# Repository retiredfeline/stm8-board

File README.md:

# A quick and simple STM8 board with TCXO

A [quick and simple STM8 clock board with TCXO](https://hackaday.io/project/184120-quick-and-simple-stm8-board-with-tcxo) to be used in a larger project.

## Versioning

First release February 2022

## Authors

* **Ken Yap**

## License

See the [LICENSE](LICENSE.md) file for license rights and limitations (MIT).

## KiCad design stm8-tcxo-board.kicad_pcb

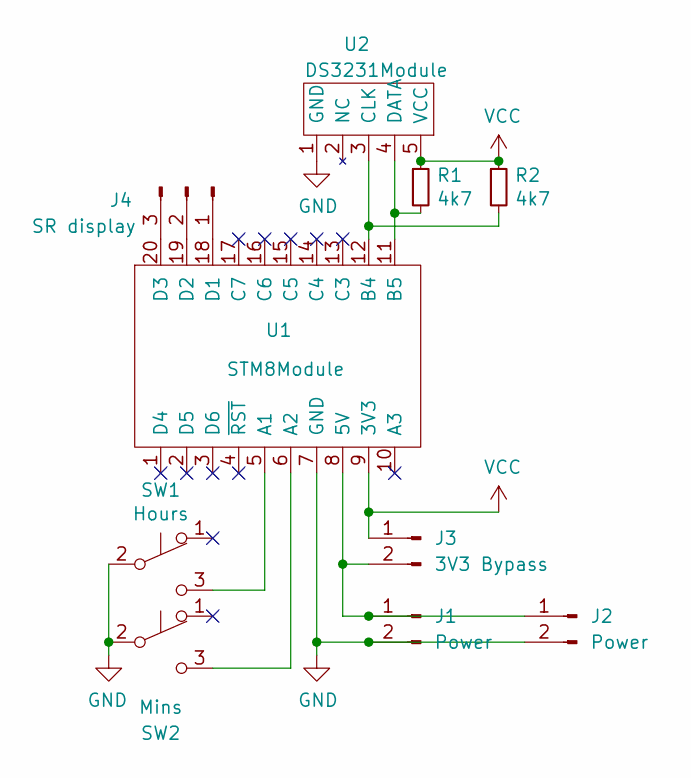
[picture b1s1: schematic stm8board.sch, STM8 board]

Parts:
J1, J2: Power; PinHeader_1x02_P2.54mm_Vertical
J3: 3V3 Bypass; PinHeader_1x02_P2.54mm_Vertical
J4: SR display; PinHeader_1x03_P2.54mm_Vertical
R1, R2: 4k7; R_Axial_DIN0207_L6.3mm_D2.5mm_P10.16mm_Horizontal
SW1: Hours; SWITCH_SPDT_PTH_11.6X4.0MM
SW2: Mins; SWITCH_SPDT_PTH_11.6X4.0MM
U1: STM8Module; DIP-20_600_ELL
U2: DS3231Module; DS3231_Module

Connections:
GND: J1.2, J2.2, SW1.2 (B), SW2.2 (B), U1.7 (GND), U2.1 (GND)
unnamed: J1.1, J2.1, J3.2, U1.8 (5V)
unnamed: J4.1, U1.18 (D1)
unnamed: J4.2, U1.19 (D2)
unnamed: J4.3, U1.20 (D3)
unnamed: R1.2, U1.11 (B5), U2.4 (DATA)
unnamed: R2.2, U1.12 (B4), U2.3 (CLK)
unnamed: SW1.3 (C), U1.5 (A1)
unnamed: SW2.3 (C), U1.6 (A2)
VCC: J3.1, R1.1, R2.1, U1.9 (3V3), U2.5 (VCC)

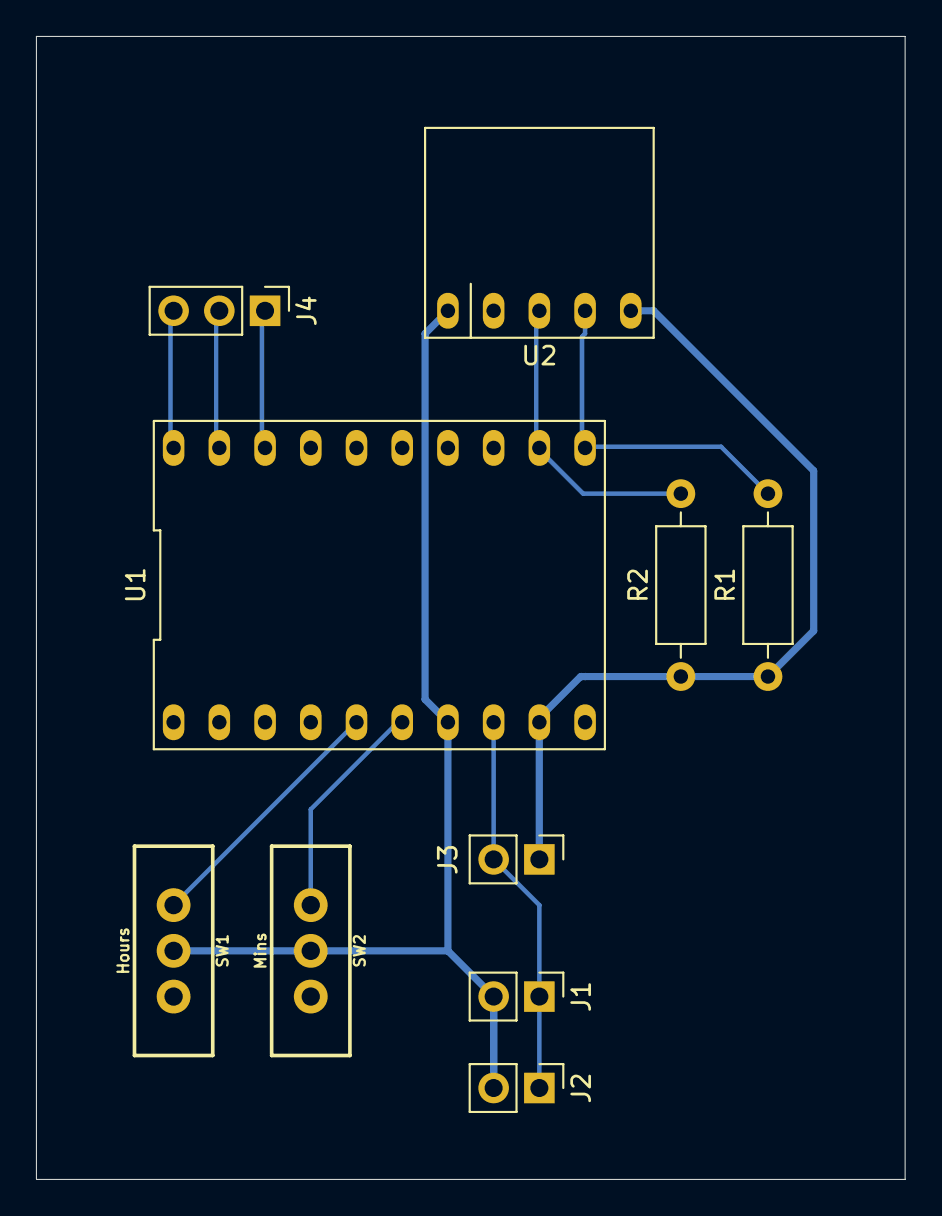
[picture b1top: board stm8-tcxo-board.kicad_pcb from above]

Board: 2 copper layers, 48.3 x 63.5 mm, 10 parts (0 on the bottom side), 10 nets.

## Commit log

2022-02-22 Initial release
2022-02-22 Add README.md
2024-05-26 Rename files
